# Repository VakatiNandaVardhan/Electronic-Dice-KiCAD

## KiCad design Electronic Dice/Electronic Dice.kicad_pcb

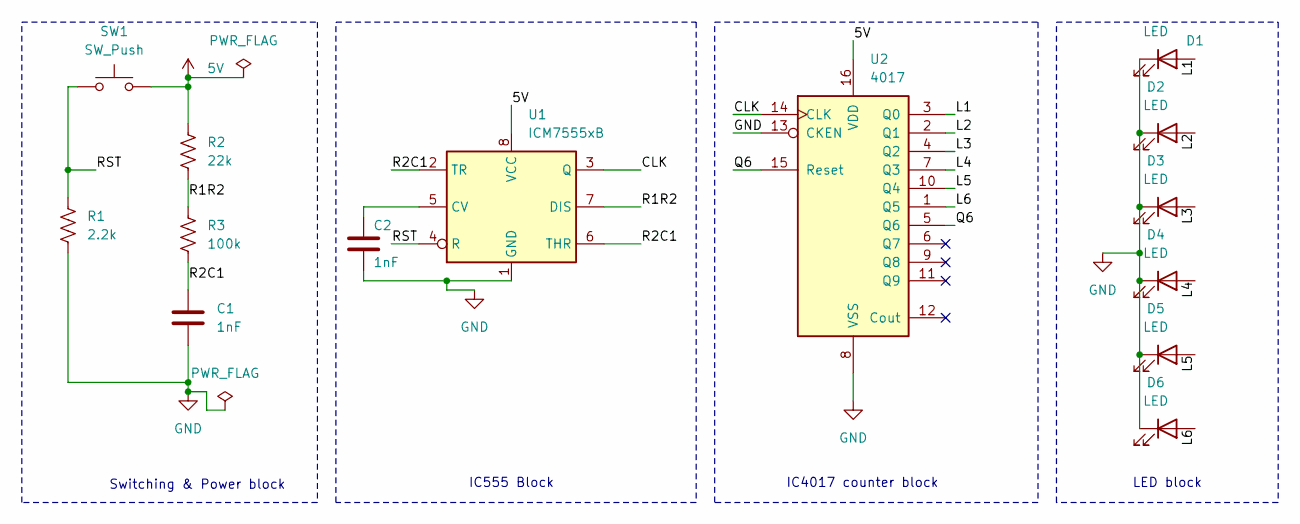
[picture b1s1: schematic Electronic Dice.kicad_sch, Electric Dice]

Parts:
C1, C2: 1nF; C_Axial_L3.8mm_D2.6mm_P10.00mm_Horizontal
D1, D2, D3, D4, D5, D6: LED; LED_D3.0mm_Horizontal_O1.27mm_Z2.0mm
R1: 2.2k; R_Axial_DIN0414_L11.9mm_D4.5mm_P15.24mm_Horizontal
R2: 22k; R_Axial_DIN0414_L11.9mm_D4.5mm_P15.24mm_Horizontal
R3: 100k; R_Axial_DIN0414_L11.9mm_D4.5mm_P15.24mm_Horizontal
SW1: SW_Push; SW_PUSH_6mm
U1: ICM7555xB; SOIC-8_3.9x4.9mm_P1.27mm
U2: 4017; DIP-16_W7.62mm

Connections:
5V: R2.1, SW1.2, U1.8 (VCC), U2.16 (VDD)
/CLK: U1.3 (Q), U2.14 (CLK)
/L1: D1.2 (A), U2.3 (Q0)
/L2: D2.2 (A), U2.2 (Q1)
/L3: D3.2 (A), U2.4 (Q2)
/L4: D4.2 (A), U2.7 (Q3)
/L5: D5.2 (A), U2.10 (Q4)
/L6: D6.2 (A), U2.1 (Q5)
/Q6: U2.5 (Q6), U2.15 (Reset)
/R1R2: R2.2, R3.1, U1.7 (DIS)
/R2C1: C1.1, R3.2, U1.2 (TR), U1.6 (THR)
/RST: R1.1, SW1.1, U1.4 (R)
GND: C1.2, C2.2, D1.1 (K), D2.1 (K), D3.1 (K), D4.1 (K), D5.1 (K), D6.1 (K), R1.2, U1.1 (GND), U2.8 (VSS), U2.13 (CKEN)
unnamed: C2.1, U1.5 (CV)

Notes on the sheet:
LED block
IC4017 counter block
Switching & Power block
IC555 Block

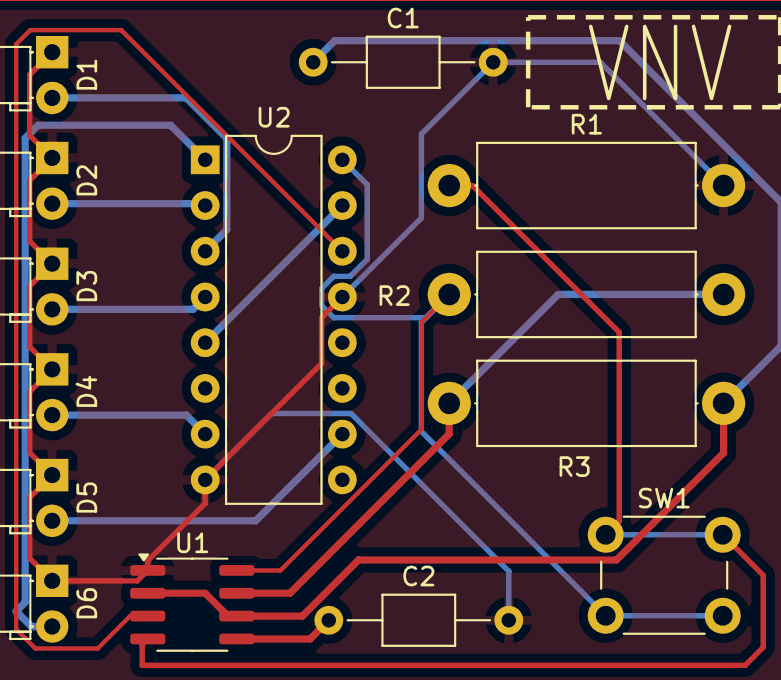
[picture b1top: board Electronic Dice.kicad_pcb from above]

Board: 2 copper layers, 14 parts (0 on the bottom side), 14 nets.
